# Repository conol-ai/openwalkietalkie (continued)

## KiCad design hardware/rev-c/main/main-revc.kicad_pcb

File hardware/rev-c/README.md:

# OpenWalkieTalkie Rev C main board (BodyV6.13 case)

Rev C is the [Rev B](../rev-b/README.md) main board re-expressed on the
current CoHDL compiler and library, with the JLCPCB BOM and placement file
produced through CoHDL supplier bindings. It was made at the maintainer's
request: "可以新作一份rev c，把包的版本和cohdl的版本都升级上去" (make a Rev C with the
package versions and the CoHDL version raised).

**Nothing electrical or physical changed.** The copper, drills, outline,
silkscreen and paste are Rev B's; a board made from this directory is the
same board as one made from `../rev-b`. What changed is how the design is
written down and where the order data comes from.

Status (2026-11-11):

| Check | Result |
|---|---|
| Rev C board vs Rev B board, in the board frame | **142 footprints, 493 pads, 1351 tracks, 477 vias, 36 zones identical**; one footprint frame turned (U4, 0° → 90°) |
| KiCad 10.0.7 DRC, zones refilled, all severities, Rev B's rules | **0 violations, 0 unconnected** |
| Gerber, paste and drill files vs Rev B's | 13 files, **identical apart from 50 header lines** (KiCad version, plot time, project name) |
| Source parity (`check.sh`) | passes: 142 footprints, 459 numbered pads, 454 pads compared in the board frame |
| Supplier-binding coverage | **6 of 124** LCSC-sourced placements come from library bindings; 118 from the fallback table |

## What changed against Rev B

| | Rev B | Rev C |
|---|---|---|
| Compiler | CoHDL 0.9.0 | CoHDL 0.10.0 (see [Compiler](#compiler)) |
| Library packages | pinned to the r6-era versions | latest versions published on registry.cohdl.org on 2026-11-11 (table below) |
| Source | `place flash … rotate 180 side bottom` | `rotate 270 side bottom`: `soic` 0.3.0 turned the SOIC-8 land a quarter turn in its own frame, so the placement angle changes to keep the pads where they are. Design renamed `OpenMicroDialRevC`; no other source line changed |
| Routed board | `main-revb.kicad_pcb` | `main-revc.kicad_pcb`: U4's footprint frame turned to match the source (angle 0° → 90°, children re-expressed so nothing moves), and 3D model paths pointed at `../rev-b/models`. 147 changed lines in total, produced by [`scripts/make_board.py`](scripts/make_board.py) |
| Design BOM | U1 manufacturer "Nsiway" | "NSIWAY" (spelling in `@contrib/audio-amp` 0.2.0); otherwise identical |
| JLC BOM / CPL | from the board by formula, LCSC numbers from a hand-kept table | from `cohdl build --supplier lcsc --bottom-rotation lcsc=mirrored` where the library binds the part, from a committed fallback table elsewhere; every row says which |
| CPL rows that differ | U4 rotation 180, J5 at (28.000, −4.000) | U4 rotation 90, J5 at (28.000, −5.550); see [ORDER-NOTES](fab-jlcpcb/ORDER-NOTES.md) |

The board's silkscreen still reads "OpenWalkieTalkie main Rev B / 2026-10" and
the title block still says revision B. Changing either would change a
Gerber, and Rev C's claim is that the Gerbers are Rev B's.

### Package versions

All from `https://registry.cohdl.org`; `source/main/cohdl.lock` records the
hashes. Written by `cohdl update`.

| Package | Rev B | Rev C |
|---|---|---|
| `@contrib/audio-amp` | 0.1.0 | 0.2.0 |
| `@contrib/display` | 0.1.0 | 0.1.0 |
| `@richtek/dcdc` | 0.1.2 | 0.1.4 |
| `@sifli/sf32` | 0.1.2 | 0.1.2 |
| `antenna` | 0.1.0 | 0.1.0 |
| `esd` | 0.1.1 | 0.1.2 |
| `flash` | 0.1.4 | 0.3.1 |
| `load-switch` | 0.1.1 | 0.2.0 |
| `mic` | 0.1.1 | 0.1.2 |
| `misc` | 0.1.1 | 0.1.1 |
| `osc` | 0.1.1 | 0.2.0 |
| `passive` | 0.2.2 | 0.2.6 |
| `qfn` | 0.2.0 | 0.3.0 |
| `soic` | 0.2.0 | 0.3.0 |
| `std` | 0.3.0 | 0.3.0 |
| `switches` | 0.1.2 | 0.1.3 |
| `usb` | 0.1.1 | 0.1.6 |

Twelve of seventeen moved. Of every library land the board uses, only
`soic::SOIC8P127X790X216N` (U4) changed geometry.

### Compiler

The build reports `cohdl 0.10.0`. CoHDL 0.10.0 is a published release: tag
`v0.10.0` (commit `2ca26c9`, 2026-11-06) with a GitHub release of the same
name. The binary used here was not the release download. It was built from
the CoHDL repository's `main` at commit `43c055e` (2026-11-11), 147 commits
after the tag. None of those commits touches `src/`, `Cargo.toml` or
`Cargo.lock`, so the compiler source is the release's; whether the release
binary gives byte-identical output was not tested.

## Files

| What | Where |
|---|---|
| CoHDL source | [`source/main/src/main.cohdl`](source/main/src/main.cohdl); [build and checks](source/README.md) |
| Routed board (KiCad 10, fabrication authority) | [`main/main-revc.kicad_pcb`](main/main-revc.kicad_pcb) with `.kicad_pro` and `.kicad_dru` copied from Rev B |
| JLCPCB order package | [`fab-jlcpcb/`](fab-jlcpcb/ORDER-NOTES.md). **Read ORDER-NOTES first.** |
| Placement preview before ordering | [`preview/`](preview/README.md): what goes through JLCPCB's assembly preview so that orientations are measured first. Two previews read on 2026-11-12 ([first](preview/2026-11-12/README.md), [second](preview/2026-11-12-iteration-2/README.md)): all 118 previewed placements confirmed, 13 of them with a board-local mapping that is now in the order CPL; 7 parts could not be previewed. |
| Design BOM / KiCad positions | [`main/assembly/bom.csv`](main/assembly/bom.csv), [`main/assembly/positions-kicad-all.csv`](main/assembly/positions-kicad-all.csv) |
| Verification reports | [`verification/`](verification/) |
| Scripts | [`scripts/`](scripts/README.md) |

Not copied, because they are unchanged and Rev C would only duplicate them:

| What | Use Rev B's |
|---|---|
| 3D models (3.9 MB) | [`../rev-b/models/`](../rev-b/models/ATTRIBUTION.md); the Rev C board references them directly |
| Populated and fit STEP files (33 MB) | [`../rev-b/3d/`](../rev-b/3d/) |
| Plot directories (`gerber/`, `stencil/`, `drill/`) | [`../rev-b/main/`](../rev-b/main/); Rev C carries only the order zip, compared file by file in [`verification/fab-compare-vs-rev-b.json`](verification/fab-compare-vs-rev-b.json) |
| UART flash jig | [`../rev-b/jig/`](../rev-b/jig/README.md) |
| Audio crosstalk, placement, 3D fit, netlist-diff and review reports | [`../rev-b/verification/`](../rev-b/verification/); they describe the same copper |
| Design notes, layout history, Chinese assembly BOM | [`../rev-b/source/main/docs/`](../rev-b/source/main/docs/), [`../rev-b/scripts/`](../rev-b/scripts/README.md), `../rev-b/openwalkietalkie-revb-bom-zh.xlsx` |

Rev B's README remains the description of the board itself: what moved from
r6, the decisions, the known limitations and the firmware notes all apply
unchanged. Firmware for Rev C hardware is the `hw-b` build.

## Build and verify

Needs CoHDL 0.10.0 (`COHDL_BIN`) and KiCad 10's Python with `pcbnew`
(`KICAD_PYTHON`; found automatically on macOS). From the repository root:

```sh
./hardware/rev-c/check.sh
```

It runs, in order:

1. `make_board.py --check`: the Rev C board is the Rev B board plus the two
   documented edits, byte for byte.
2. `pad_identity.py`: every pad (number, net, centre, size as it lies on the
   board, shape, type, drill, layers), track, via, zone and graphic equals
   Rev B's. Footprint angles are reported, not compared.
3. `build_source.py`: `cohdl install`, then `cohdl build --emit kicad_pcb
   --supplier lcsc --bottom-rotation lcsc=mirrored`, then the population
   flags from `assembly.json`.
4. `check_source.py`: Rev B's parity check against the Rev C board, plus a
   comparison of every primary pad in the board frame.
5. `build_fab.py --check`: the committed BOM, CPL, orientation list and
   sourcing record are what the source and library produce now, and no DNP
   site, test point or mounting hole appears in them.
6. `compare_fab.py`: the order zip's 13 files equal Rev B's apart from
   header metadata.

It writes only under `source/main/out/`. DRC and the Gerber export are not
part of it; see [`scripts/README.md`](scripts/README.md).

### Why the board-frame pad check

Raising `soic` from 0.2.0 to 0.3.0 with the Rev B placement line compiles
with no error and no warning, and puts U4's eight pads a quarter turn away
from the routed copper. Only a comparison against the board catches it.
[`verification/unmigrated-u4-check.txt`](verification/unmigrated-u4-check.txt)
is `check.sh` run on that source: it fails on all eight pads. The check
compares where each pad's copper lies on the board, so it does not depend on
which angle a footprint reports.

## Known limitations

Rev B's [known limitations](../rev-b/README.md#known-limitations) all apply.
Specific to Rev C:

1. **118 of 124 LCSC numbers still come from a table**, not from the
   library. The published `passive` 0.2.6 binds no resistor, and the JLC
   Basic resistors this board orders (UniOhm 0402WGF, 43 placements) have no
   library binding at all yet. The six bound placements are C12, C19, C20,
   C22, J5 and U4.
2. **Only two CPL rows carry a checked frame.** U4 and J5 come out of the
   library binding and differ from Rev B's file. The other 123 rows are the
   same uncorrected convention values as Rev B (119 of them for unbound
   parts, 4 for bound capacitors whose map is zero). Two placement previews
   on 2026-11-12 ([first](preview/2026-11-12/README.md),
   [second](preview/2026-11-12-iteration-2/README.md)) read 118 rows. 105
   were right; 13 were wrong (U1, U2, U10, U20, U7, U8, U3, J1, J3, SW1,
   SW2, SW5, SW6) and now carry a board-local mapping from
   [`source/main/placement-evidence.csv`](source/main/placement-evidence.csv),
   read right with it applied. Seven rows (U5, Y1, AE1, R32, SW3, SW4, MK1)
   were not read at all.
3. **The library evidence for U4 and J5 was taken on other boards**
   (preview records dated 2026-10-30). The 2026-11-12 preview confirmed
   both on this board. Neither has been compared with what was actually
   placed on Rev B boards; see the open questions.
4. **R39's pads.** On the routed board R39's two pads lie 0.64 × 0.54 mm;
   the `passive::CHIP_0402` land is 0.54 × 0.64 mm. The centres agree. This
   is on the Rev B board already (its check compared nominal pad sizes and
   did not see it). Rev C keeps the copper and the library part, and
   `check_source.py` allows exactly this transposition on exactly these two
   pads. Making the source agree would mean a design-local land for R39,
   which would take it off the land future library resistor bindings are
   measured on.
5. **Pad-shape equivalence in the source** is as in Rev B: the SKTD switch
   frame lands and the charger's paste windows are built from overlapping
   primitives, and pads that repeat a number are not shape-audited.
6. **DRC was run with KiCad 10.0.7**; Rev B's report is from 10.0.4. Rev B's
   board gives the same 0 / 0 under 10.0.7.
7. **U4's 3D model** was turned back with its frame. Bottom-side renders of
   both boards match; the model is symmetric under a half turn, so the
   render cannot tell −90° from +90°.
8. **CoHDL has no population concept.** `cohdl build --supplier` lists DNP
   sites and test points in its BOM and CPL. `build_fab.py` removes them
   using `assembly.json` and fails if one reaches an order file.

## Open questions for the maintainer

1. **Compiler.** Is released 0.10.0 the version Rev C should pin? The
   binary used was built from `main` at `43c055e`; its compiler source
   equals the `v0.10.0` tag.
2. **As-ordered files.** The Rev B boards were ordered with the BOM and
   placement file edited in JLC's interface (stock substitutions and
   coordinates), so neither Rev B's committed files nor these are what was
   placed. Could the as-ordered BOM and CPL be exported from JLC's order
   history? They would replace the guesswork in ORDER-NOTES, and show
   whether the U4 and J5 values here match the corrections made by hand.
3. **Wait for resistor bindings?** `passive` with the Yageo RC0402
   bindings is not published yet, and bindings for the UniOhm parts this
   board actually orders do not exist. Should Rev C merge now at 6 of 124,
   or wait until more of the BOM can come from the library?
4. **Board marking.** Should a later Rev C change the silkscreen and title
   block to say Rev C? It would change one silkscreen Gerber.
5. **R39.** Leave the transposed pads as they are (current choice), or fix
   the copper in a revision that changes copper anyway?

## License

As for Rev B: the design files here are CERN-OHL-P-2.0, see
[`../LICENSE`](../LICENSE) and [`../README.md`](../README.md). Everything
under `scripts/`, and `check.sh`, is software under the repository's MIT
license. Third-party models keep their own licenses, see
`../rev-b/models/ATTRIBUTION.md`.

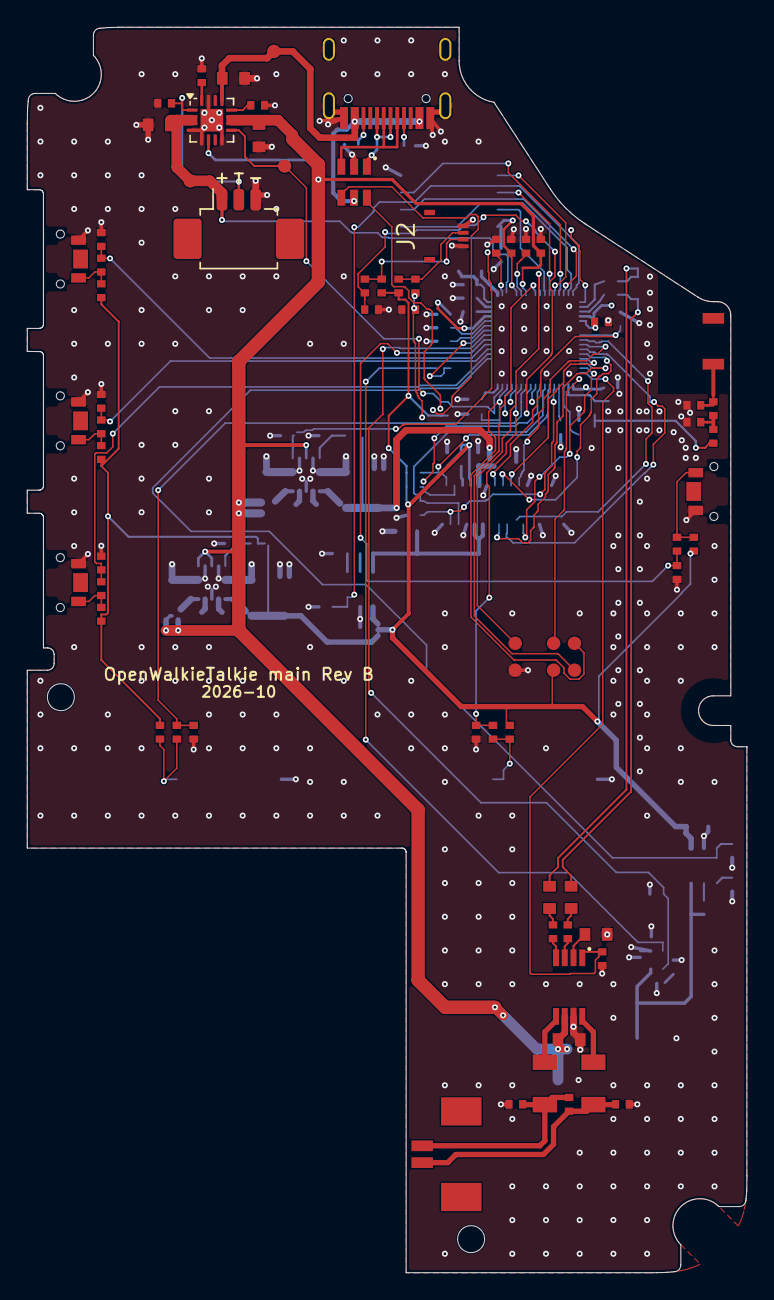
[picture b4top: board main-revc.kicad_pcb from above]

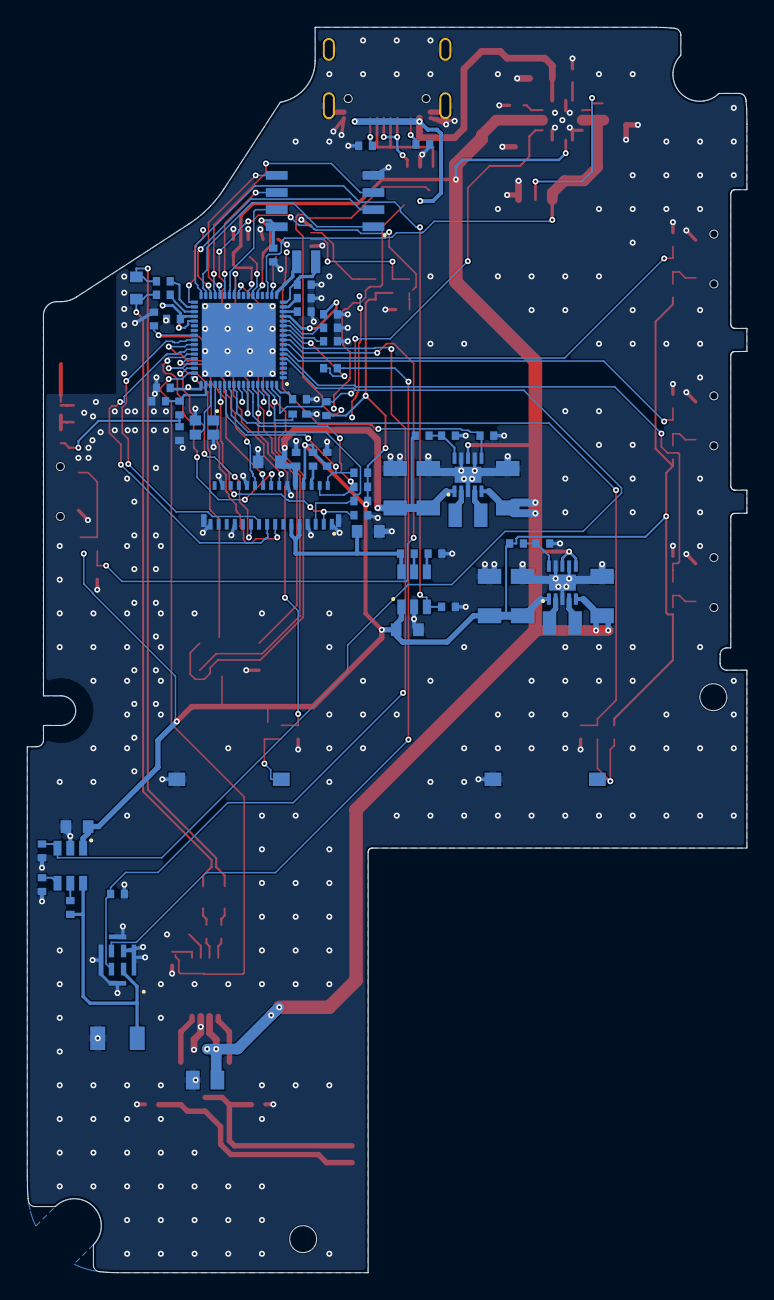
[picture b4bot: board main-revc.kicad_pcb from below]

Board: 4 copper layers, 53.4 x 92.4 mm, 142 parts (67 on the bottom side), 105 nets.

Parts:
AE1: CeramicAntenna2450; antenna-FP_ANT_2450AT18B100E
C1, C3, C4, C5, C11, C21, C49: 1uF; passive-CHIP_0603
C2: 1.5nF; passive-CHIP_0603
C6, C32, C33, C34, C35, C36, C37, C38, C39, C50: 1nF; passive-CHIP_0402
C7: 100nF; passive-CHIP_1206
C8, C9, C10: 330pF; passive-CHIP_0402
C12: 10uF; passive-CHIP_0805
C13, C17, C28, C29, C30: 4.7uF; passive-CHIP_0402
C14, C16, C23, C24, C27, C31: 2.2uF; passive-CHIP_0402
C15, C26: 1uF; passive-CHIP_0402
C18, C40, C41, C48: 4.7uF; passive-CHIP_0603
C19, C20, C22: 100nF; passive-CHIP_0402
C25: 470nF; passive-CHIP_0402
C42, C43, C44, C45, C46, C47: 10uF; passive-CHIP_1206
C52, C53, C58: NF; passive-CHIP_0402
C57: 15pF; passive-CHIP_0402
J1: PicoBlade2Pin; openmicrodial_rev_a-FP_MOLEX_53261_0271
J2: FH34SRJ_4S_0P5SH_99; openmicrodial_rev_a-FP_HIROSE_FH34SRJ_4S
J3: 53261-0371; openmicrodial_rev_b-FP_MOLEX_53261_0371
J5: USB_C_Receptacle_2_0; usb-connectors-type_c-FP_USB_C_Receptacle_HRO_TYPE_C_31_M_12
L1, L2: SpeakerFerrite600R; openmicrodial_rev_a-FP_MURATA_BLM31PG_1P5A_REFLOW
L3: 4.7uH; passive-FP_L_WPN201610U_2016Metric
L4, L5: 2.2uH; passive-FP_L_0806_2016Metric
L6: NF; passive-CHIP_0402
MH2, MH4: Mounting hole; openmicrodial_rev_b-MountingHole_2.0mm_NPTH
MK1: MP34DT05TR-A; openmicrodial_rev_a-FP_ST_MP34DT05_HCLGA_3x4
R1, R2, R8, R20, R21, R22, R23, R24, R25, R26, R27, R35: 1kohm; passive-CHIP_0402
R3, R7, R12, R13, R14, R15, R16, R17, R18, R19, R30, R41, R45, R46: 100kohm; passive-CHIP_0402
R4, R5: 22kohm; passive-CHIP_0402
R6: 22ohm; passive-CHIP_0402
R9, R34, R36, R39, R42: 1Mohm; passive-CHIP_0402
R10, R11: 5.1kohm; passive-CHIP_0402
R28, R29, R44: 10kohm; passive-CHIP_0402
R31: 86.6kohm; passive-CHIP_0402
R32: 604kohm; passive-CHIP_0402
R37: 3.6kohm; passive-CHIP_0402
R38: 3.3kohm; passive-CHIP_0402
R40, R47, R48: 0ohm; passive-CHIP_0402
R43: 180kohm; passive-CHIP_0402
SW1, SW2, SW5, SW6: SKTDLDE010; openmicrodial_rev_a-FP_ALPS_SKTDLDE010
SW3, SW4: TactileSwitchSPST; switches-FP_CK_PTS636SM25
TP1, TP2, TP3, TP4, TP5, TP6, TP7, TP8, TP9, TP10: TestPoint; misc-FP_TEST_POINT_ROUND_1MM
U1: NS4150B; contrib_audio_amp-SOP8P65X490X110N
U2, U10: TPS22918; load_switch-FP_TI_DBV0006A
U3: H0216F002AM; openmicrodial_rev_a-FP_DIANWEI_8_03A5_031250
U4: W25Q128JV; soic-SOIC8P127X790X216N
U5: SF32LB525UC6; openmicrodial_rev_b-FP_SF32LB52X_QFN68L_BSide
U6: BQ24073RGTR; openmicrodial_rev_a-FP_TI_RGT_VQFN16_3x3_EP1p68
U7, U8: RT6150B; qfn-QFN10N50P250X250_1EP120X200
U20: USBLC6; esd-FP_SOT_23_6
Y1: Crystal_4pad; osc-FP_Crystal_SMD_2016_4Pin_E1SB

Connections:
ADC_REF: C13.1, U5.68
AMP_ENABLE: R3.1, U1.1, U5.50
AUDIO_REF: C15.1, U5.39
BT_RF: C52.1, C57.1, U5.53
BUCK_FB: C17.1, L3.2, U5.17
BUCK_LX: L3.1, U5.18
CAL: TP3.1, U5.51
CC1: J5.A5, R10.1
CC2: J5.B5, R11.1
CELL: C40.1, J3.1, TP2.1, U5.20, U6.2, U6.3
DAC_N: R2.1, U5.36
DAC_P: R1.1, U5.37
DEBUG_RX_SWDIO: TP6.1, U5.27
DEBUG_TX_SWCLK: TP8.1, U5.26
ENC_A: C38.1, R26.2, U5.61
ENC_B: C39.1, R27.2, U5.60
ENTER: C33.1, R21.2, U5.8
ESC: C34.1, R22.2, U5.7
FLASH_CLK: U4.6, U5.29
FLASH_CS: U4.1, U5.33
FLASH_IO0: U4.5, U5.30
FLASH_IO1: U4.2, U5.32
FLASH_IO2: U4.3, U5.31
FLASH_IO3: U4.7, U5.28
GND: C1.2, C5.2, C6.2, C7.2, C8.2, C9.2, C11.2, C12.2, C13.2, C14.2, C15.2, C16.2, C17.2, C18.2, C19.2, C20.2, C21.2, C22.2, C23.2, C24.2, C25.2, C26.2, C27.2, C28.2, C29.2, C30.2, C31.2, C32.2, C33.2, C34.2, C35.2, C36.2, C37.2, C38.2, C39.2, C40.2, C41.2, C42.2, C43.2, C44.2, C45.2, C46.2, C47.2, C48.2, C49.2, C50.2, C52.2, C53.2, C58.2, J2.1, J2.4, J3.3, J5.A1, J5.A12, J5.B1, J5.B12, J5.SH1, J5.SH2, J5.SH3, J5.SH4, L6.2, MK1.2, MK1.5, R3.2, R7.2, R9.2, R10.2, R11.2, R30.2, R31.2, R34.2, R36.2, R37.2, R38.2, R39.2, R43.2, R44.2, R45.2, SW1.1, SW2.1, SW3.2, SW4.2, SW5.1, SW6.1, TP4.1, U1.7, U2.2, U3.1, U3.7, U3.12, U3.22, U3.25, U3.28, U3.31, U3.MP, U4.4, U5.69, U6.4, U6.5, U6.8, U6.15, U6.17, U7.3, U7.7, U7.9, U7.11, U8.3, U8.7, U8.9, U8.11, U10.2, U20.2, Y1.2, Y1.4
I2C_SCL: R29.2, U3.5, U5.58
I2C_SDA: R28.2, U3.4, U5.59
IO_3V3: C5.1, C20.1, C43.1, C44.1, C49.1, R12.1, R13.1, R14.1, R15.1, R16.1, R17.1, R18.1, R19.1, R28.1, R29.1, R41.1, R42.1, R46.2, R48.1, TP10.1, U2.1, U3.8, U7.1, U10.1
MACRO_LEFT: C36.1, R24.2, U5.63
MACRO_RIGHT: C37.1, R25.2, U5.62
MCU_LDO1: C14.1, C22.1, C23.1, U4.8, U5.22, U5.38
MCU_LDO2: C24.1, U5.14
MCU_VSYS: C16.1, C31.1, U5.19, U5.52
MIC_PDM_CLK: R6.1, U5.11
MIC_PDM_DATA: MK1.4, R7.1, U5.10
MIC_POWER_ENABLE: R9.1, U2.3, U5.5
PANEL_4V: C18.1, C19.1, C46.1, C47.1, R32.1, U3.10, U8.1
PANEL_CLK: U3.18, U5.47
PANEL_CS: U3.15, U5.48
PANEL_D0: U3.16, U5.46
PANEL_D1: U3.17, U5.45
PANEL_D2: U3.20, U5.44
PANEL_D3: U3.19, U5.43
PANEL_ENABLE: R34.1, U5.35, U8.6
PANEL_LOGIC: C21.1, R35.1, U3.9, U3.11, U10.6
PANEL_RESET: R30.1, U3.14, U5.42
PANEL_TE: U3.21, U5.49
PANEL_VCI_ENABLE: R36.1, U5.34, U10.3
PTT: C32.1, R20.2, U5.9
RESET_ACTIVE_HIGH: R39.1, TP5.1, U5.66
RETENTION: C25.1, U5.13
RTC: C26.1, U5.12
SHIFT: C35.1, R23.2, U5.6
SIP_1V8: C27.1, U5.23
SYSTEM_SUPPLY: C11.1, C12.1, C28.1, C42.1, C45.1, C48.1, TP7.1, U1.6, U5.24, U6.6, U6.10, U6.11, U7.5, U7.6, U7.8, U8.5, U8.8
TOUCH_IRQ: R41.2, U3.2, U5.57
TOUCH_RESET: R45.1, U3.3, U5.56
TP_VCC: R48.2, U3.6
USB_C_N: J5.A7, J5.B7, U20.3
USB_C_P: J5.A6, J5.B6, U20.1
USB_MCU_N: U5.64, U20.4
USB_MCU_P: U5.65, U20.6
USB_VBUS: C41.1, J5.A4, J5.A9, J5.B4, J5.B9, TP9.1, U6.13, U20.5
VOUT1: C29.1, U5.16
VOUT2: C30.1, U5.15
XTAL48_XI: U5.55, Y1.1
XTAL48_XO: U5.54, Y1.3
audio::AC_N: C4.2, R5.1
audio::AC_P: C3.2, R4.1
audio::AMP_BYPASS: C1.1, U1.2
audio::AMP_INN: R5.2, U1.4
audio::AMP_INP: R4.2, U1.3
audio::AMP_VON: L2.1, U1.5
audio::AMP_VOP: L1.1, U1.8
audio::DAC_FILTER_N: C2.2, C4.1, R2.2
audio::DAC_FILTER_P: C2.1, C3.1, R1.2
audio::MIC_CLOCK: MK1.3, R6.2
audio::MIC_DISCHARGE: R8.1, U2.5
audio::MIC_SLEW: C6.1, U2.4
audio::MIC_SUPPLY: C7.1, MK1.1, R8.2, U2.6
audio::SPEAKER_MINUS: C9.1, C10.2, J1.2, L2.2
audio::SPEAKER_PLUS: C8.1, C10.1, J1.1, L1.2
controls::ENC_A_CONTACT: J2.2, R18.2, R26.1
controls::ENC_B_CONTACT: J2.3, R19.2, R27.1
controls::ENTER_CONTACT: R13.2, R21.1, SW1.2
controls::ESC_CONTACT: R14.2, R22.1, SW2.2
controls::MACRO_LEFT_CONTACT: R16.2, R24.1, SW3.1
controls::MACRO_RIGHT_CONTACT: R17.2, R25.1, SW4.1
controls::PTT_CONTACT: R12.2, R20.1, SW5.2
controls::SHIFT_CONTACT: R15.2, R23.1, SW6.2
power::CELL_TEMPERATURE: J3.2, R44.1, U6.1
power::CHG_ILIM: R38.1, U6.12
power::CHG_ISET: R37.1, U6.16
power::CHG_STATUS: R46.1, TP1.1, U5.67, U6.9
power::IO_FB: R42.2, R43.1, U7.10
power::IO_LX1: L4.1, U7.4
power::IO_LX2: L4.2, U7.2
power::PANEL_FB: R31.1, R32.2, U8.10
power::PANEL_LX1: L5.1, U8.4
power::PANEL_LX2: L5.2, U8.2
power::VCI_DISCHARGE: R35.2, U10.5
power::VCI_SLEW: C50.1, U10.4
rf::ANT_MATCH: L6.1, R40.2, R47.1
rf::BT_ANT: AE1.1, C58.1, R47.2
rf::BT_RF_LINE: C53.1, C57.2, R40.1

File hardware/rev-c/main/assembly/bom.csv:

Comment,Designator,Footprint,Manufacturer,MPN,Quantity
2450AT18B100E,AE1,FP_ANT_2450AT18B100E,Johanson Technology,2450AT18B100E,1
1uF,"C1,C3,C4,C5,C11,C21,C49",CHIP_0603,Yageo,CC0603KRX5R6BB105,7
1.5nF,C2,CHIP_0603,Yageo,CC0603JRNPO9BN152,1
1nF,"C6,C32,C33,C34,C35,C36,C37,C38,C39,C50",CHIP_0402,Yageo,CC0402JRNPO9BN102,10
100nF,C7,CHIP_1206,Yageo,CC1206JRNPO8BN104,1
330pF,"C8,C9,C10",CHIP_0402,Yageo,CC0402JRNPO9BN331,3
10uF,C12,CHIP_0805,Yageo,CC0805KRX5R8BB106,1
4.7uF,"C13,C17,C29,C30",CHIP_0402,Samsung Electro-Mechanics,CL05A475MP5NRNC,4
2.2uF,"C14,C16,C23,C24,C27,C31",CHIP_0402,Samsung Electro-Mechanics,CL05A225KP5NSNC,6
1uF,"C15,C26",CHIP_0402,Samsung Electro-Mechanics,CL05A105KA5NQNC,2
4.7uF,"C18,C40,C41,C48",CHIP_0603,Yageo,CC0603KRX5R6BB475,4
100nF,"C19,C20,C22",CHIP_0402,Yageo,CC0402KRX7R7BB104,3
470nF,C25,CHIP_0402,Yageo,CC0402KRX5R6BB474,1
4.7uF,C28,CHIP_0402,Samsung Electro-Mechanics,CL05A475MP5NRNC,1
10uF,"C42,C43,C44,C45,C46,C47",CHIP_1206,TDK,C3216X7R1C106K160AC,6
15pF,C57,CHIP_0402,FH (Guangdong Fenghua),0402CG150J500NT,1
53261-0271,J1,FP_MOLEX_53261_0271,Molex,53261-0271,1
FH34SRJ-4S-0.5SH(99),J2,FP_HIROSE_FH34SRJ_4S,Hirose,FH34SRJ-4S-0.5SH(99),1
53261-0371,J3,FP_MOLEX_53261_0371,Molex,53261-0371,1
TYPE-C-31-M-12,J5,FP_USB_C_Receptacle_HRO_TYPE_C_31_M_12,HRO,TYPE-C-31-M-12,1
SpeakerFerrite600R,"L1,L2",FP_MURATA_BLM31PG_1P5A_REFLOW,Murata,BLM31PG601SN1L,2
4.7uH,L3,FP_L_WPN201610U_2016Metric,Sunlord,WPN201610U4R7MT,1
2.2uH,"L4,L5",FP_L_0806_2016Metric,Murata,DFE201612E-2R2M=P2,2
MP34DT05TR-A,MK1,FP_ST_MP34DT05_HCLGA_3x4,STMicroelectronics,MP34DT05TR-A,1
1kohm,"R1,R2,R8,R20,R21,R22,R23,R24,R25,R26,R27,R35",CHIP_0402,Yageo,RC0402FR-071KL,12
100kohm,"R3,R7,R12,R13,R14,R15,R16,R17,R18,R19,R30,R41",CHIP_0402,Yageo,RC0402FR-07100KL,12
22kohm,"R4,R5",CHIP_0402,Yageo,RC0402FR-0722KL,2
22ohm,R6,CHIP_0402,Yageo,RC0402FR-0722RL,1
1Mohm,"R9,R34,R36,R39,R42",CHIP_0402,Yageo,RC0402FR-071ML,5
5.1kohm,"R10,R11",CHIP_0402,Yageo,RC0402FR-075K1L,2
10kohm,"R28,R29",CHIP_0402,Yageo,RC0402FR-0710KL,2
86.6kohm,R31,CHIP_0402,Yageo,RC0402FR-0786K6L,1
604kohm,R32,CHIP_0402,Yageo,RC0402FR-07604KL,1
3.6kohm,R37,CHIP_0402,Yageo,RC0402FR-073K6L,1
3.3kohm,R38,CHIP_0402,Yageo,RC0402FR-073K3L,1
0ohm,"R40,R47",CHIP_0402,Yageo,RC0402JR-070RL,2
180kohm,R43,CHIP_0402,Yageo,RC0402FR-07180KL,1
100kohm,R45,CHIP_0402,Yageo,RC0402FR-07100KL,1
100kohm,R46,CHIP_0402,Yageo,RC0402FR-07100KL,1
0ohm,R48,CHIP_0402,Yageo,RC0402JR-070RL,1
SKTDLDE010,"SW1,SW2,SW5,SW6",FP_ALPS_SKTDLDE010,Alps Alpine,SKTDLDE010,4
PTS636SM25SMTRLFS,"SW3,SW4",FP_CK_PTS636SM25,C&K,PTS636SM25SMTRLFS,2
NS4150B,U1,SOP8P65X490X110N,NSIWAY,NS4150B,1
TPS22918DBVR,"U2,U10",FP_TI_DBV0006A,Texas Instruments,TPS22918DBVR,2
8.03A5.031250,U3,FP_DIANWEI_8_03A5_031250,DIANWEI,8.03A5.031250,1
W25Q128JVSIQ,U4,SOIC8P127X790X216N,Winbond,W25Q128JVSIQ,1
SF32LB525UC6,U5,FP_SF32LB52X_QFN68L_BSide,SiFli Technologies,SF32LB525UC6,1
BQ24073RGTR,U6,FP_TI_RGT_VQFN16_3x3_EP1p68,Texas Instruments,BQ24073RGTR,1
RT6150BGQW,"U7,U8",QFN10N50P250X250_1EP120X200,Richtek,RT6150BGQW,2
USBLC6-2SC6,U20,FP_SOT_23_6,STMicroelectronics,USBLC6-2SC6,1
E1SB48E001G00E,Y1,FP_Crystal_SMD_2016_4Pin_E1SB,Hosonic,E1SB48E001G00E,1

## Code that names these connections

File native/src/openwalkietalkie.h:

#ifndef OPENWALKIETALKIE_H
#define OPENWALKIETALKIE_H
#include <stdbool.h>
#include <stddef.h>
#include <stdint.h>

/* Rust entry points: application thread only. */
uint32_t owt_core_init(void);
/* Reload preferences after BLE_POWER_ON_IND initializes the SDK's NVDS. */
void owt_core_load_ui_prefs(void);
bool owt_core_poll(uint32_t now_ms);
struct owt_region { uint16_t x0, y0, x1, y1; }; /* Exclusive, even end coordinates. */
bool owt_core_begin_frame(bool force);
/* Returned rectangles are physical panel coordinates; pixels already have
 * mounting rotation applied and retain a 480-pixel source stride. */
const uint8_t *owt_core_draw_next(uint8_t slot, struct owt_region *region);
/* index is a physical panel band, not a logical UI band. */
const uint8_t *owt_core_draw_splash_band(uint16_t index);
uint32_t owt_core_splash_duration(void);
/* Panel mounting built into the Rust core: 0 (LilyGo board) or 180 (hw-a,
 * hw-b), and the board itself: 0 LilyGo, 1 Rev A, 2 Rev B. */
uint16_t owt_core_rotation(void);
uint8_t owt_core_board(void);
void owt_core_hid_connected(bool connected);
void owt_core_bluetooth_rssi(int8_t rssi);
void owt_core_hid_report(const uint8_t *data, size_t len);
uint8_t owt_core_battery_percent(void);
/* Write cached battery state into the 38-byte battery diagnostic core tail.
 * Application thread only; this never starts ADC or charger transactions. */
void owt_core_battery_diagnostic(uint8_t *data);
enum owt_screen { OWT_SCREEN_ACTIVE, OWT_SCREEN_DIM, OWT_SCREEN_OFF };
uint8_t owt_core_screen(void);
uint8_t owt_core_brightness(void);
uint32_t owt_core_wait_ms(void);
void owt_core_frame_ready(void);
void owt_core_panel_slept(void);
void owt_core_wake(uint32_t now);

enum owt_message_type {
    OWT_BLE_READY, OWT_CONNECTED, OWT_DISCONNECTED, OWT_REPORT,
    OWT_CCCD, OWT_ENCRYPTED, OWT_BT_EVENT, OWT_WAKE_DISPLAY, OWT_DIAGNOSE,
    OWT_RSSI,
};
struct owt_message {
    uint8_t type, conn_idx;
    uint16_t event_type, event_id;
    uint32_t epoch;
    uint8_t length;
    uint8_t data[64];
};
bool owt_post(const struct owt_message *message);
void owt_wake(void);
void owt_bluetooth_start(void);
void owt_bluetooth_message(const struct owt_message *message);
void owt_bluetooth_battery(uint8_t percent);
void owt_bluetooth_poll(uint32_t now);
int owt_hid_notify(const uint8_t *data, size_t length);
void owt_hid_disconnect(void);
/* Device-owned UI preferences, a shared versioned/checksummed 64-byte record.
 * Application thread only. Missing/corrupt storage falls back to English. */
bool owt_ui_prefs_read(uint8_t *bytes, size_t length);
bool owt_ui_prefs_write(const uint8_t *bytes, size_t length);
void owt_board_start(void);
/* Rev A's six buttons and wheel on GPIOs: an edge since the last call, and the
 * raw levels as src/input/direct.rs expects them (bit 0 PTT PA24, 1 ENTER
 * PA25, 2 ESC PA26, 3 SHIFT PA27, 4 LEFT PA37, 5 RIGHT PA38, 6 encoder A
 * PA39, 7 encoder B PA40; a set bit is a high, released pin). The dev board
 * answers false and 0xFF. */
bool owt_inputs_asserted(void);
uint8_t owt_inputs_read(void);
#ifdef OWT_BOARD_HW_B
/* Rev B: the BQ24073's CHG output on PA33 reads low while the cell charges. */
bool owt_charger_charging(void);
#endif
void owt_audio_poll(uint32_t now_ms);
void owt_display_band(uint16_t index, const uint8_t *pixels);
void owt_display_region(const struct owt_region *region, const uint8_t *pixels);
bool owt_display_busy(void);
void owt_display_on(void);
void owt_display_enable(void);
void owt_display_sleep(void);
void owt_display_wake(void);
void owt_display_reset(bool asserted);
void owt_board_diagnose(void);
bool owt_diagnostic_report(const uint8_t *data, size_t len);
void owt_display_brightness(uint8_t level);
void owt_power_stats(uint32_t now, uint8_t screen);
void owt_idle_power_start(void);
void owt_idle_power_ui(bool active);
void owt_idle_power_stats(void);
#endif
